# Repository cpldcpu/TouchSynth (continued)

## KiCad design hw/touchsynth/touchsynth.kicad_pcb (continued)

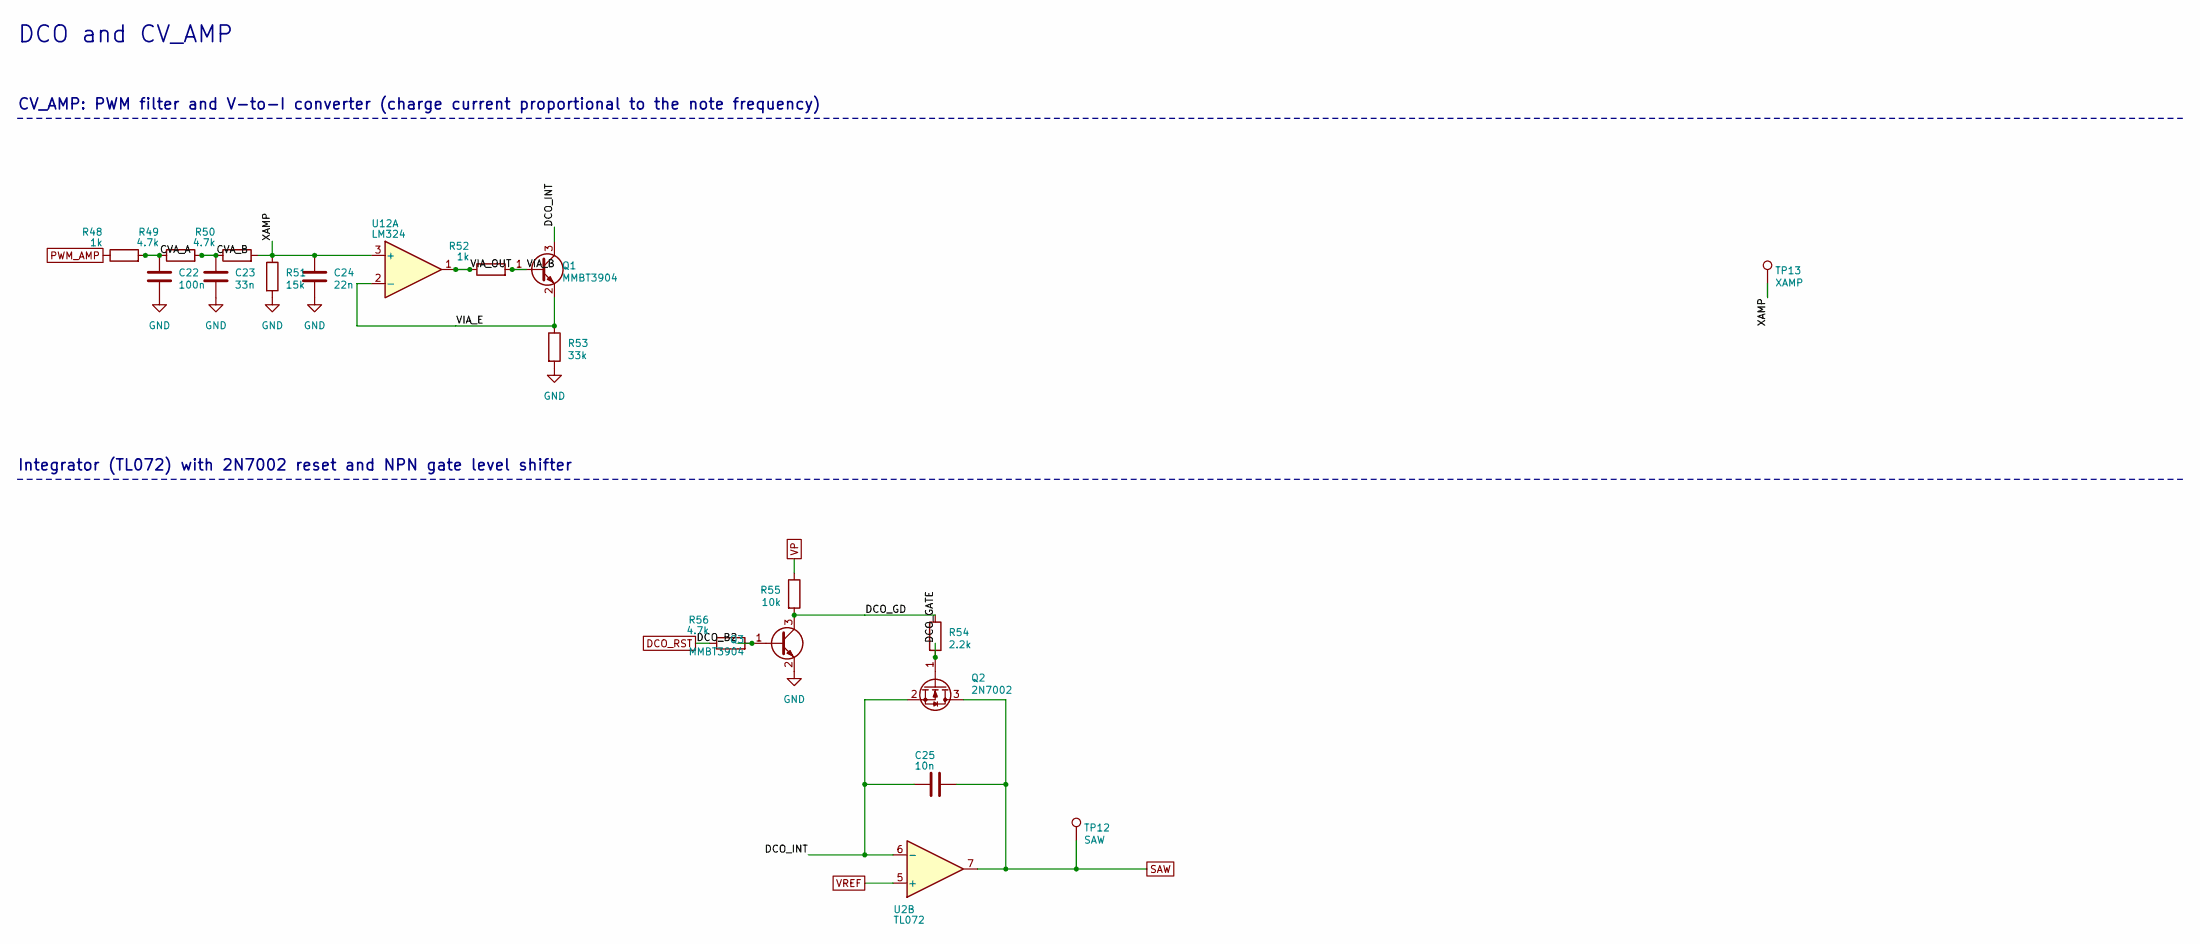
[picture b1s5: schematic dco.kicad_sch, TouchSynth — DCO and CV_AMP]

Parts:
C22: 100n; C_0603_1608Metric; LCSC C14663
C23: 33n; C_0603_1608Metric; LCSC C21117
C24: 22n; C_0603_1608Metric; LCSC C21122
C25: 10n; C_0603_1608Metric; LCSC C57112
Q1, Q3: MMBT3904; SOT-23; LCSC C20526
Q2: 2N7002; SOT-23; LCSC C8545
R48, R52: 1k; R_0603_1608Metric; LCSC C21190
R49, R50, R56: 4.7k; R_0603_1608Metric; LCSC C23162
R51: 15k; R_0603_1608Metric; LCSC C22809
R53: 33k; R_0603_1608Metric; LCSC C4216
R54: 2.2k; R_0603_1608Metric; LCSC C4190
R55: 10k; R_0603_1608Metric; LCSC C25804
TP12: SAW; TestPoint_Pad_D1.0mm
TP13: XAMP; TestPoint_Pad_D1.0mm
U2: TL072; SOIC-8_3.9x4.9mm_P1.27mm; LCSC C6961
U12: LM324; SOIC-14_3.9x8.7mm_P1.27mm; LCSC C71035

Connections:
/dco/CVA_A: C22.1, R48.2, R49.1
/dco/CVA_B: C23.1, R49.2, R50.1
/dco/DCO_B2: Q3.1 (B), R56.2
/dco/DCO_GATE: Q2.1 (G), R54.2
/dco/DCO_GD: Q3.3 (C), R54.1, R55.2
/dco/DCO_INT: C25.2, Q1.3 (C), Q2.2 (S), U2.6 (-)
/dco/VIA_B: Q1.1 (B), R52.2
/dco/VIA_E: Q1.2 (E), R53.1, U12.2 (-)
/dco/VIA_OUT: R52.1, U12.1
/dco/XAMP: C24.1, R50.2, R51.1, TP13.1, U12.3 (+)
DCO_RST: R56.1; also elsewhere on the board
GND: C22.2, C23.2, C24.2, Q3.2 (E), R51.2, R53.2; also elsewhere on the board
PWM_AMP: R48.1; also elsewhere on the board
SAW: C25.1, Q2.3 (D), TP12.1, U2.7; also elsewhere on the board
VP: R55.1; also elsewhere on the board
VREF: U2.5 (+); also elsewhere on the board

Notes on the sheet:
DCO and CV_AMP
CV_AMP: PWM filter and V-to-I converter (charge current proportional to the note frequency)
Integrator (TL072) with 2N7002 reset and NPN gate level shifter

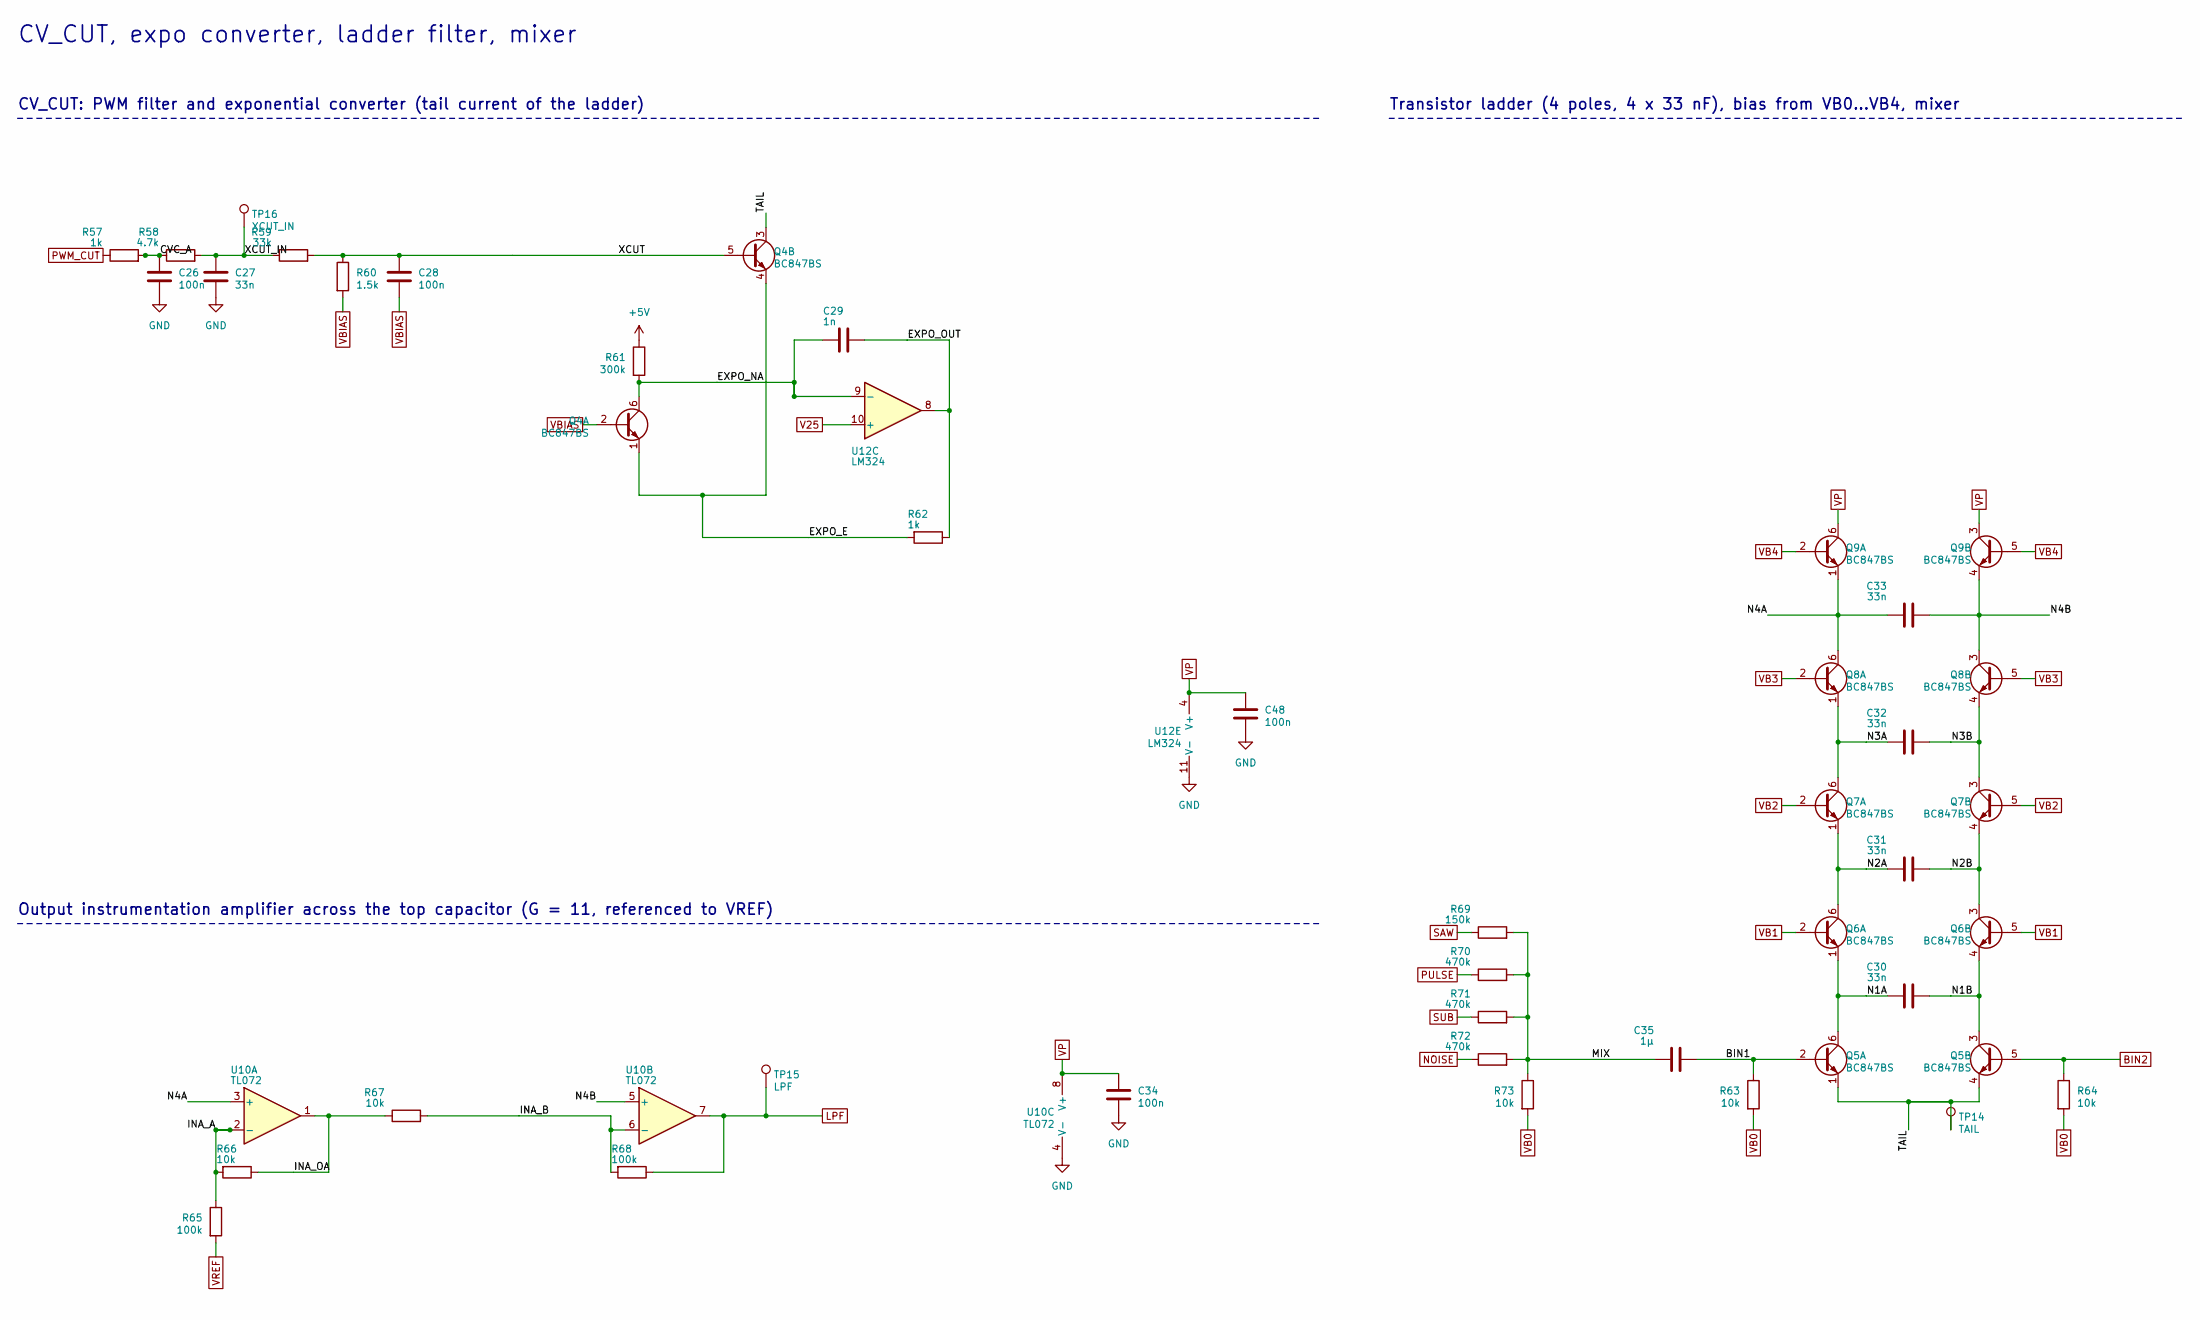
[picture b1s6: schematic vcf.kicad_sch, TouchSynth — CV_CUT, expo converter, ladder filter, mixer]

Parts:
C26, C28, C34, C48: 100n; C_0603_1608Metric; LCSC C14663
C27, C30, C31, C32, C33: 33n; C_0603_1608Metric; LCSC C21117
C29: 1n; C_0603_1608Metric; LCSC C1588
C35: 1µ; C_0603_1608Metric; LCSC C15849
Q4, Q5, Q6, Q7, Q8, Q9: BC847BS; SOT-363_SC-70-6; LCSC C41375126
R57, R62: 1k; R_0603_1608Metric; LCSC C21190
R58: 4.7k; R_0603_1608Metric; LCSC C23162
R59: 33k; R_0603_1608Metric; LCSC C4216
R60: 1.5k; R_0603_1608Metric; LCSC C22843
R61: 300k; R_0603_1608Metric; LCSC C23024
R63, R64, R66, R67, R73: 10k; R_0603_1608Metric; LCSC C25804
R65, R68: 100k; R_0603_1608Metric; LCSC C25803
R69: 150k; R_0603_1608Metric; LCSC C22807
R70, R71, R72: 470k; R_0603_1608Metric; LCSC C23178
TP14: TAIL; TestPoint_Pad_D1.0mm
TP15: LPF; TestPoint_Pad_D1.0mm
TP16: XCUT_IN; TestPoint_Pad_D1.0mm
U10: TL072; SOIC-8_3.9x4.9mm_P1.27mm; LCSC C6961
U12: LM324; SOIC-14_3.9x8.7mm_P1.27mm; LCSC C71035

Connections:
+5V: R61.1; also elsewhere on the board
/vcf/BIN1: C35.2, Q5.2 (B1), R63.1
/vcf/CVC_A: C26.1, R57.2, R58.1
/vcf/EXPO_E: Q4.1 (E1), Q4.4 (E2), R62.2
/vcf/EXPO_NA: C29.2, Q4.6 (C1), R61.2, U12.9 (-)
/vcf/EXPO_OUT: C29.1, R62.1, U12.8
/vcf/INA_A: R65.1, R66.2, U10.2 (-)
/vcf/INA_B: R67.2, R68.2, U10.6 (-)
/vcf/INA_OA: R66.1, R67.1, U10.1
/vcf/MIX: C35.1, R69.2, R70.2, R71.2, R72.2, R73.1
/vcf/N1A: C30.1, Q5.6 (C1), Q6.1 (E1)
/vcf/N1B: C30.2, Q5.3 (C2), Q6.4 (E2)
/vcf/N2A: C31.1, Q6.6 (C1), Q7.1 (E1)
/vcf/N2B: C31.2, Q6.3 (C2), Q7.4 (E2)
/vcf/N3A: C32.1, Q7.6 (C1), Q8.1 (E1)
/vcf/N3B: C32.2, Q7.3 (C2), Q8.4 (E2)
/vcf/N4A: C33.1, Q8.6 (C1), Q9.1 (E1), U10.3 (+)
/vcf/N4B: C33.2, Q8.3 (C2), Q9.4 (E2), U10.5 (+)
/vcf/TAIL: Q4.3 (C2), Q5.1 (E1), Q5.4 (E2), TP14.1
/vcf/XCUT: C28.1, Q4.5 (B2), R59.2, R60.1
/vcf/XCUT_IN: C27.1, R58.2, R59.1, TP16.1
BIN2: Q5.5 (B2), R64.1; also elsewhere on the board
GND: C26.2, C27.2, C34.2, C48.2, U10.4 (V-), U12.11 (V-); also elsewhere on the board
LPF: R68.1, TP15.1, U10.7; also elsewhere on the board
NOISE: R72.1; also elsewhere on the board
PULSE: R70.1; also elsewhere on the board
PWM_CUT: R57.1; also elsewhere on the board
SAW: R69.1; also elsewhere on the board
SUB: R71.1; also elsewhere on the board
V25: U12.10 (+); also elsewhere on the board
VB0: R63.2, R64.2, R73.2; also elsewhere on the board
VB1: Q6.2 (B1), Q6.5 (B2); also elsewhere on the board
VB2: Q7.2 (B1), Q7.5 (B2); also elsewhere on the board
VB3: Q8.2 (B1), Q8.5 (B2); also elsewhere on the board
VB4: Q9.2 (B1), Q9.5 (B2); also elsewhere on the board
VBIAS: C28.2, Q4.2 (B1), R60.2; also elsewhere on the board
VP: C34.1, C48.1, Q9.3 (C2), Q9.6 (C1), U10.8 (V+), U12.4 (V+); also elsewhere on the board
VREF: R65.2; also elsewhere on the board

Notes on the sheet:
CV_CUT, expo converter, ladder filter, mixer
CV_CUT: PWM filter and exponential converter (tail current of the ladder)
Transistor ladder (4 poles, 4 x 33 nF), bias from VB0...VB4, mixer
Output instrumentation amplifier across the top capacitor (G = 11, referenced to VREF)

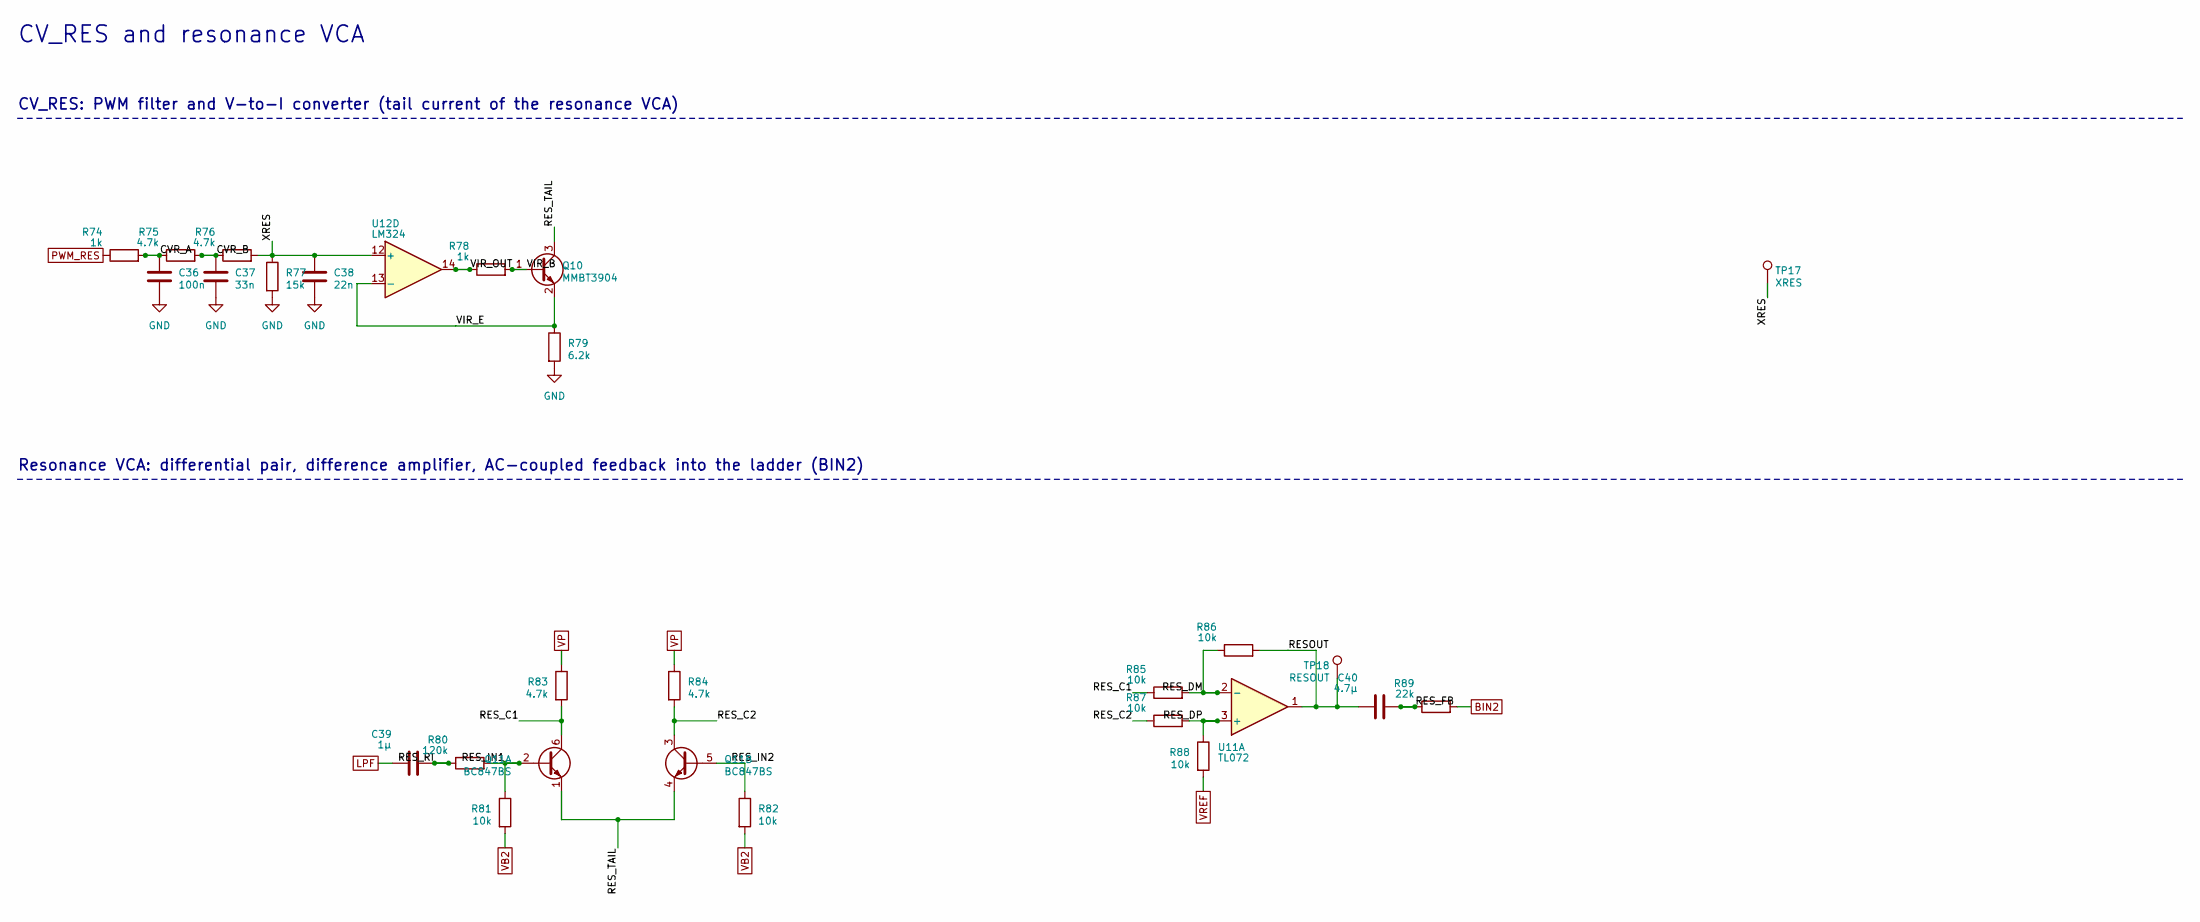
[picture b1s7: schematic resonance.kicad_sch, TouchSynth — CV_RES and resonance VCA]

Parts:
C36: 100n; C_0603_1608Metric; LCSC C14663
C37: 33n; C_0603_1608Metric; LCSC C21117
C38: 22n; C_0603_1608Metric; LCSC C21122
C39: 1µ; C_0603_1608Metric; LCSC C15849
C40: 4.7µ; C_0603_1608Metric; LCSC C19666
Q10: MMBT3904; SOT-23; LCSC C20526
Q11: BC847BS; SOT-363_SC-70-6; LCSC C41375126
R74, R78: 1k; R_0603_1608Metric; LCSC C21190
R75, R76, R83, R84: 4.7k; R_0603_1608Metric; LCSC C23162
R77: 15k; R_0603_1608Metric; LCSC C22809
R79: 6.2k; R_0603_1608Metric; LCSC C4260
R80: 120k; R_0603_1608Metric; LCSC C25808
R81, R82, R85, R86, R87, R88: 10k; R_0603_1608Metric; LCSC C25804
R89: 22k; R_0603_1608Metric; LCSC C31850
TP17: XRES; TestPoint_Pad_D1.0mm
TP18: RESOUT; TestPoint_Pad_D1.0mm
U11: TL072; SOIC-8_3.9x4.9mm_P1.27mm; LCSC C6961
U12: LM324; SOIC-14_3.9x8.7mm_P1.27mm; LCSC C71035

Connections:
/resonance/CVR_A: C36.1, R74.2, R75.1
/resonance/CVR_B: C37.1, R75.2, R76.1
/resonance/RESOUT: C40.1, R86.2, TP18.1, U11.1
/resonance/RES_C1: Q11.6 (C1), R83.2, R85.1
/resonance/RES_C2: Q11.3 (C2), R84.2, R87.1
/resonance/RES_DM: R85.2, R86.1, U11.2 (-)
/resonance/RES_DP: R87.2, R88.1, U11.3 (+)
/resonance/RES_FB: C40.2, R89.1
/resonance/RES_IN1: Q11.2 (B1), R80.2, R81.1
/resonance/RES_IN2: Q11.5 (B2), R82.1
/resonance/RES_RI: C39.2, R80.1
/resonance/RES_TAIL: Q10.3 (C), Q11.1 (E1), Q11.4 (E2)
/resonance/VIR_B: Q10.1 (B), R78.2
/resonance/VIR_E: Q10.2 (E), R79.1, U12.13 (-)
/resonance/VIR_OUT: R78.1, U12.14
/resonance/XRES: C38.1, R76.2, R77.1, TP17.1, U12.12 (+)
BIN2: R89.2; also elsewhere on the board
GND: C36.2, C37.2, C38.2, R77.2, R79.2; also elsewhere on the board
LPF: C39.1; also elsewhere on the board
PWM_RES: R74.1; also elsewhere on the board
VB2: R81.2, R82.2; also elsewhere on the board
VP: R83.1, R84.1; also elsewhere on the board
VREF: R88.2; also elsewhere on the board

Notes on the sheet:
CV_RES and resonance VCA
CV_RES: PWM filter and V-to-I converter (tail current of the resonance VCA)
Resonance VCA: differential pair, difference amplifier, AC-coupled feedback into the ladder (BIN2)

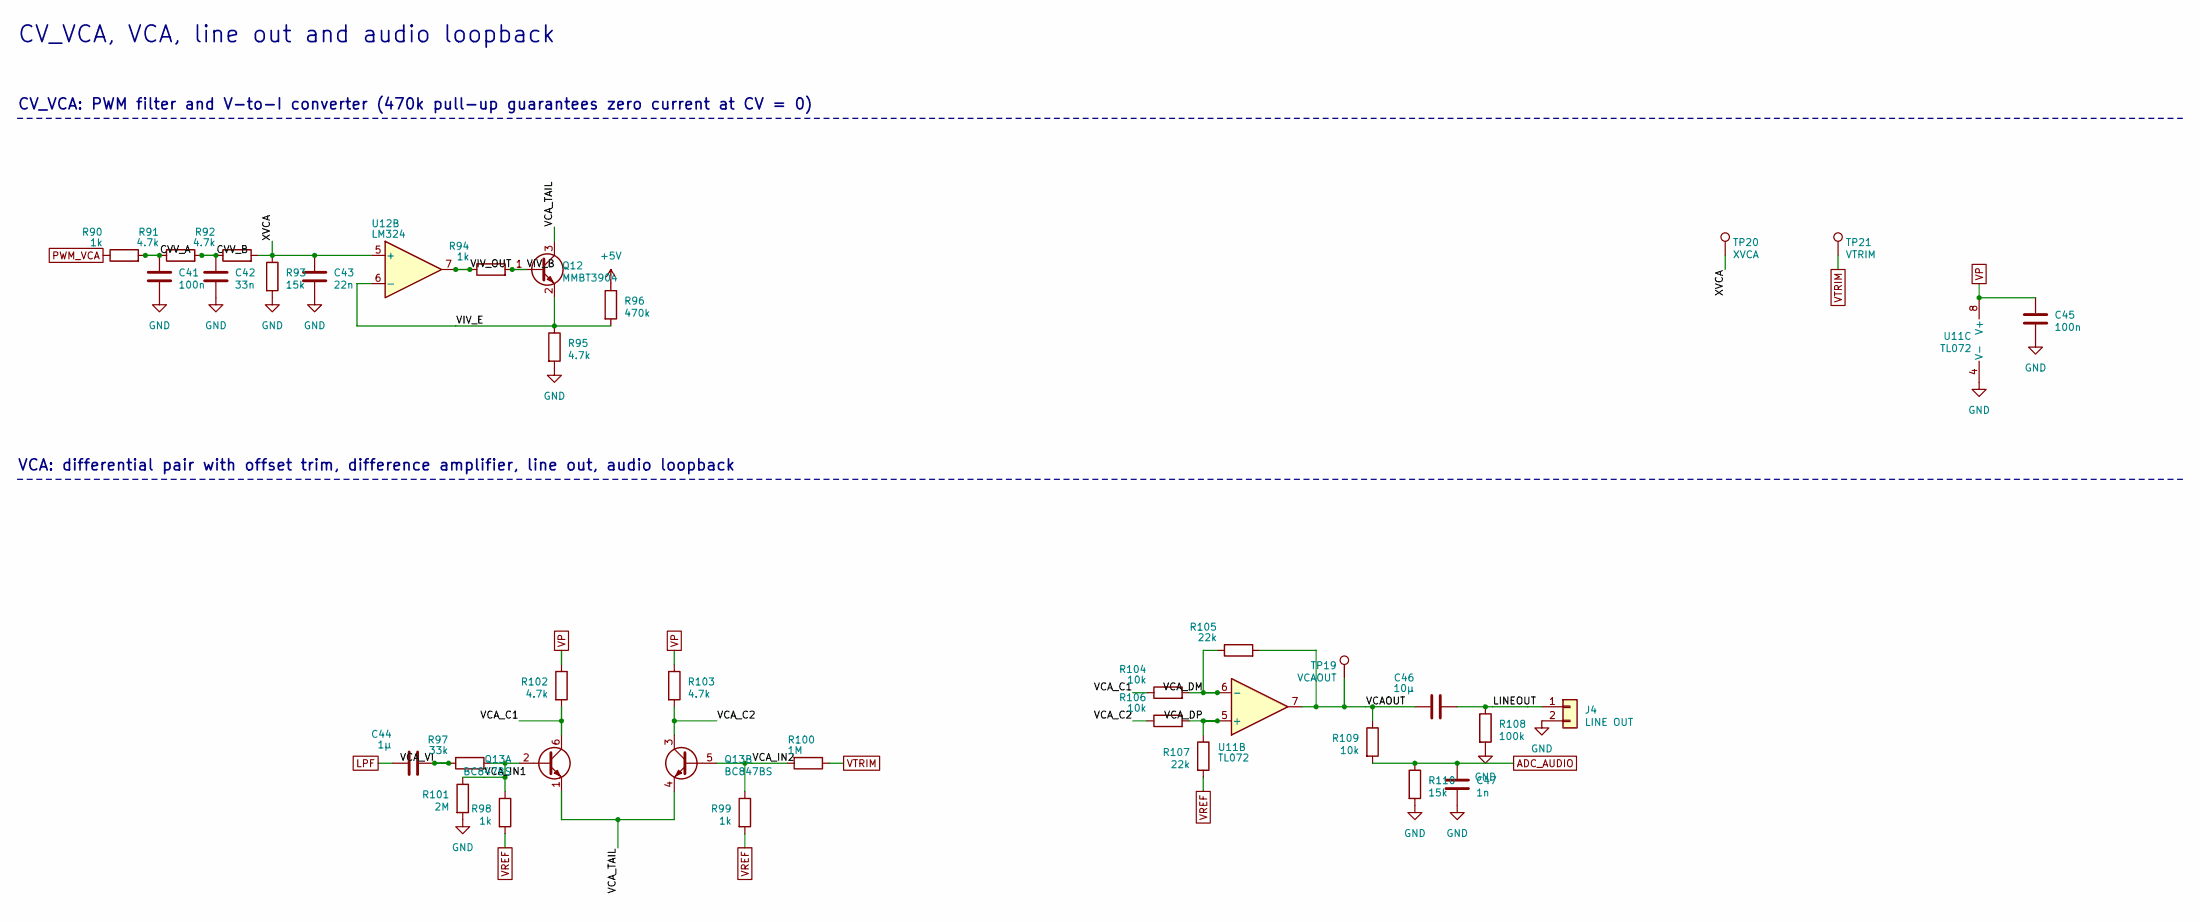
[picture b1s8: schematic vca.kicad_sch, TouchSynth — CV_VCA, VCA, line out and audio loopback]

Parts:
C41, C45: 100n; C_0603_1608Metric; LCSC C14663
C42: 33n; C_0603_1608Metric; LCSC C21117
C43: 22n; C_0603_1608Metric; LCSC C21122
C44: 1µ; C_0603_1608Metric; LCSC C15849
C46: 10µ; C_0603_1608Metric; LCSC C19702
C47: 1n; C_0603_1608Metric; LCSC C1588
J4: LINE OUT; PinHeader_1x02_P2.54mm_Vertical
Q12: MMBT3904; SOT-23; LCSC C20526
Q13: BC847BS; SOT-363_SC-70-6; LCSC C41375126
R90, R94, R98, R99: 1k; R_0603_1608Metric; LCSC C21190
R91, R92, R95, R102, R103: 4.7k; R_0603_1608Metric; LCSC C23162
R93, R110: 15k; R_0603_1608Metric; LCSC C22809
R96: 470k; R_0603_1608Metric; LCSC C23178
R97: 33k; R_0603_1608Metric; LCSC C4216
R100: 1M; R_0603_1608Metric; LCSC C22935
R101: 2M; R_0603_1608Metric; LCSC C22976
R104, R106, R109: 10k; R_0603_1608Metric; LCSC C25804
R105, R107: 22k; R_0603_1608Metric; LCSC C31850
R108: 100k; R_0603_1608Metric; LCSC C25803
TP19: VCAOUT; TestPoint_Pad_D1.0mm
TP20: XVCA; TestPoint_Pad_D1.0mm
TP21: VTRIM; TestPoint_Pad_D1.0mm
U11: TL072; SOIC-8_3.9x4.9mm_P1.27mm; LCSC C6961
U12: LM324; SOIC-14_3.9x8.7mm_P1.27mm; LCSC C71035

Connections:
+5V: R96.1; also elsewhere on the board
/vca/CVV_A: C41.1, R90.2, R91.1
/vca/CVV_B: C42.1, R91.2, R92.1
/vca/LINEOUT: C46.2, J4.1, R108.1
/vca/VCAOUT: C46.1, R105.2, R109.1, TP19.1, U11.7
/vca/VCA_C1: Q13.6 (C1), R102.2, R104.1
/vca/VCA_C2: Q13.3 (C2), R103.2, R106.1
/vca/VCA_DM: R104.2, R105.1, U11.6 (-)
/vca/VCA_DP: R106.2, R107.1, U11.5 (+)
/vca/VCA_IN1: Q13.2 (B1), R97.2, R98.1, R101.1
/vca/VCA_IN2: Q13.5 (B2), R99.1, R100.2
/vca/VCA_TAIL: Q12.3 (C), Q13.1 (E1), Q13.4 (E2)
/vca/VCA_VI: C44.2, R97.1
/vca/VIV_B: Q12.1 (B), R94.2
/vca/VIV_E: Q12.2 (E), R95.1, R96.2, U12.6 (-)
/vca/VIV_OUT: R94.1, U12.7
/vca/XVCA: C43.1, R92.2, R93.1, TP20.1, U12.5 (+)
ADC_AUDIO: C47.1, R109.2, R110.1; also elsewhere on the board
GND: C41.2, C42.2, C43.2, C45.2, C47.2, J4.2, R93.2, R95.2, R101.2, R108.2, R110.2, U11.4 (V-); also elsewhere on the board
LPF: C44.1; also elsewhere on the board
PWM_VCA: R90.1; also elsewhere on the board
VP: C45.1, R102.1, R103.1, U11.8 (V+); also elsewhere on the board
VREF: R98.2, R99.2, R107.2; also elsewhere on the board
VTRIM: R100.1, TP21.1; also elsewhere on the board

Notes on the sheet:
CV_VCA, VCA, line out and audio loopback
CV_VCA: PWM filter and V-to-I converter (470k pull-up guarantees zero current at CV = 0)
VCA: differential pair with offset trim, difference amplifier, line out, audio loopback

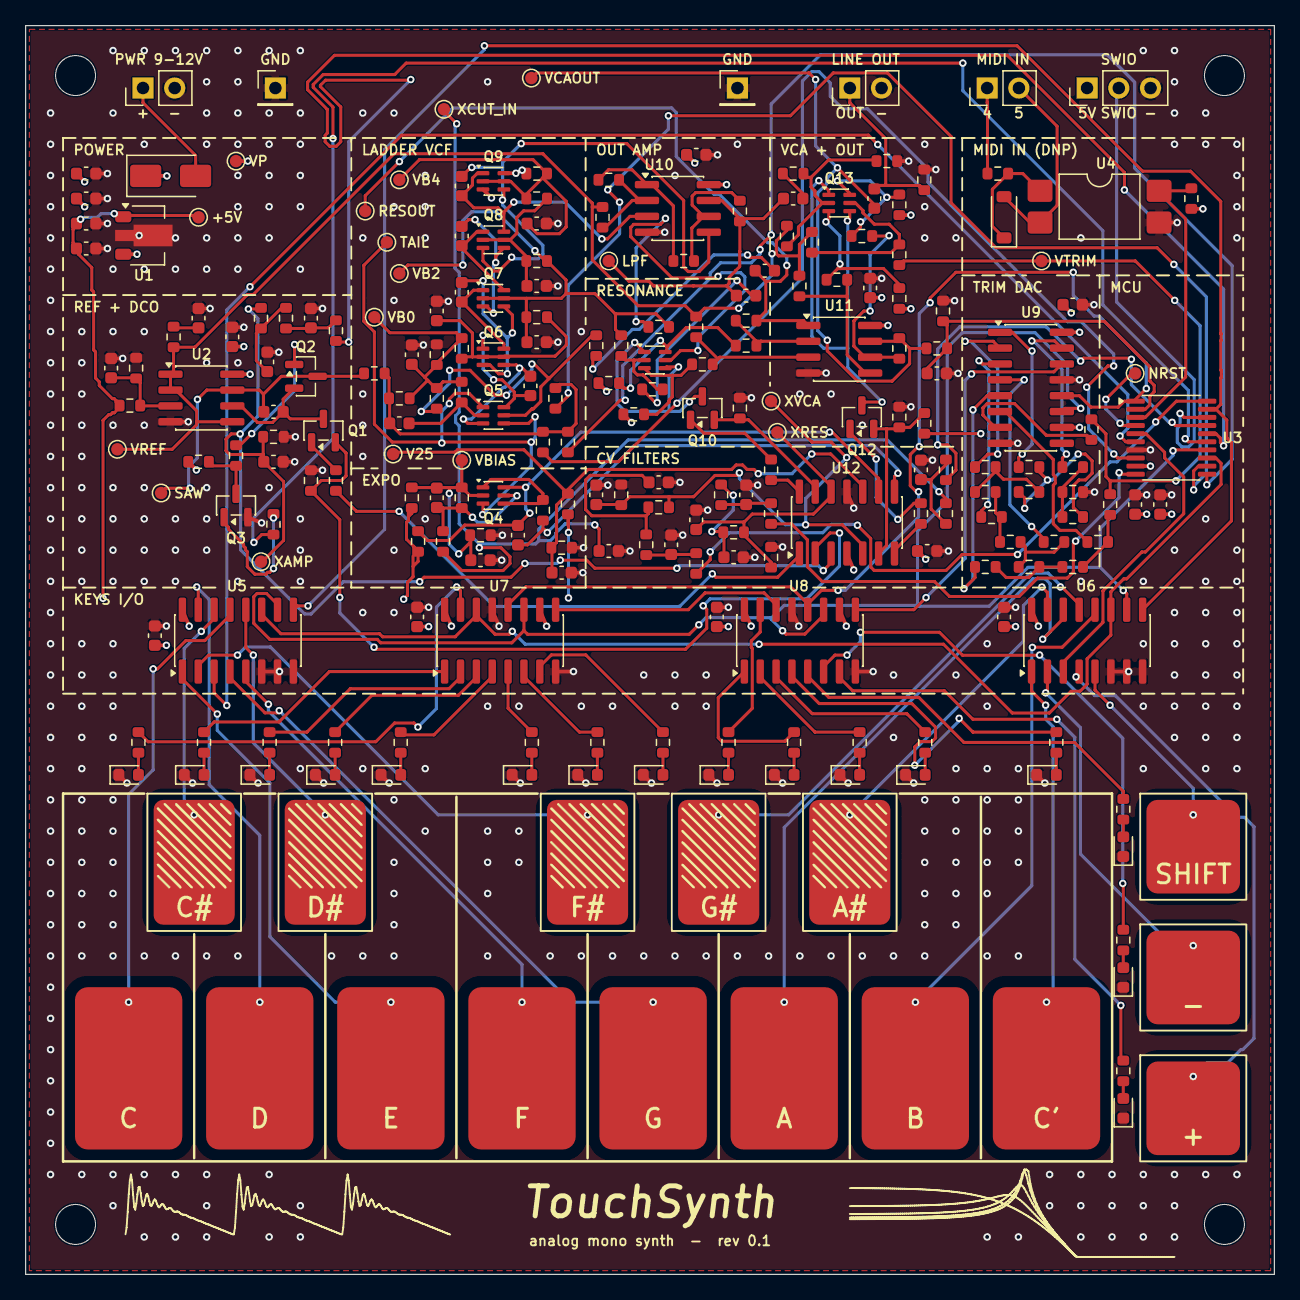
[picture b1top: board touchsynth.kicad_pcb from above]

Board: 4 copper layers, 100.0 x 100.0 mm, 246 parts (0 on the bottom side), 166 nets.

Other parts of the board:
H1, H2, H3, H4: M3; MountingHole_3.2mm_M3

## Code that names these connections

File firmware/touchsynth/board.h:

/* TouchSynth board definition: pins from hw/design.py (MCU U3, TSSOP-20), remap codes per chip family.
 *
 *  pin port  net          use                         pin port  net          use
 *   1  PD4   LATCH        74HC595 RCLK (GPIO)          11  PC1   SUB          sub-oscillator (GPIO)
 *   2  PD5   ADC_AUDIO    ADC IN5 <- audio loopback    12  PC2   PULSE        TIM2 CH2
 *   3  PD6   MIDI_RX      USART1 RX                    13  PC3   S0_DATA      mux S0 / 595 SER
 *   4  PD7   NRST                                      14  PC4   S1_CLK       mux S1 / 595 SRCLK
 *   5  PA1   TOUCH_B      mux B common, ADC IN1        15  PC5   DCO_RST      TIM2 CH1 (active low)
 *   6  PA2   TOUCH_A      mux A common, ADC IN0        16  PC6   PWM_AMP      TIM1 CH1
 *   8  PD0   NOISE        noise (GPIO)                 17  PC7   PWM_CUT      TIM1 CH2
 *  10  PC0   PWM_RES      TIM1 CH3                     18  PD1   SWIO
 *                                                       19  PD2   S2           mux S2 (GPIO)
 *                                                       20  PD3   PWM_VCA      TIM1 CH4
 *
 * Timer remaps (checked against the CH32V003 reference header and the CH32V002 datasheet pin table):
 *   CH32V003: TIM1 partial remap 1 (01b): CH1 PC6, CH2 PC7, CH3 PC0, CH4 PD3
 *             TIM2 partial remap 1 (01b): CH1 PC5, CH2 PC2
 *   CH32V00x: TIM1_RM = 0010b: TIM1_CH1_2 PC6, TIM1_CH2_2 PC7, TIM1_CH3_2 PC0, TIM1_CH4_2 PD3
 *             TIM2_RM = 010b:  TIM2_CH1_ETR_2 PC5, TIM2_CH2_2 PC2
 * The complementary / break functions these remaps also route (TIM1 CH1N PC3, CH2N PC4, CH3N PD1, BKIN PC1,
 * TIM2 CH3 PD2, CH4 PC1) are never enabled.
 */
#ifndef BOARD_H
#define BOARD_H

#include "ch32fun.h"

#define PIN_LATCH    PD4
#define PIN_AUDIO    PD5
#define PIN_MIDI_RX  PD6
#define PIN_TOUCH_B  PA1
#define PIN_TOUCH_A  PA2
#define PIN_NOISE    PD0
#define PIN_CV_RES   PC0
#define PIN_SUB      PC1
#define PIN_PULSE    PC2
#define PIN_S0_DATA  PC3
#define PIN_S1_CLK   PC4
#define PIN_DCO_RST  PC5
#define PIN_CV_AMP   PC6
#define PIN_CV_CUT   PC7
#define PIN_S2       PD2
#define PIN_CV_VCA   PD3

#define ADC_CH_TOUCH_A 0
#define ADC_CH_TOUCH_B 1
#define ADC_CH_AUDIO   5

#if defined(CH32V003)
#define CHIP_NAME "CH32V003"
#define REMAP_MASK   (AFIO_PCFR1_TIM1_REMAP | AFIO_PCFR1_TIM2_REMAP)
#define REMAP_BITS   (AFIO_PCFR1_TIM1_REMAP_PARTIALREMAP1 | AFIO_PCFR1_TIM2_REMAP_PARTIALREMAP1)
#elif defined(CH32V00x)
#if defined(CH32V002)
#define CHIP_NAME "CH32V002"
#elif defined(CH32V006)
#define CHIP_NAME "CH32V006"
#else
#define CHIP_NAME "CH32V00x"
#endif
#define REMAP_MASK   (AFIO_PCFR1_TIM1_RM | AFIO_PCFR1_TIM2_RM)
#define REMAP_BITS   (AFIO_PCFR1_TIM1_RM_1 | AFIO_PCFR1_TIM2_RM_1)       /* TIM1_RM = 0010b, TIM2_RM = 010b */
#else
#error "unsupported MCU"
#endif

/* timer register bits (identical on both families; the vendor headers name them differently) */
#define T_CEN      0x0001
#define T_UDIS     0x0002
#define T_ARPE     0x0080
#define T_CMS1     0x0020   /* centre-aligned mode 1 (counts up and down) */
#define T_UIE      0x0001
#define T_UIF      0x0001
#define T_UDE      0x0100   /* DMAINTENR: DMA request on update */
#define T_UG       0x0001
#define T_MOE      0x8000
#define T_OC_PWM1_LO  0x0068   /* OCxM = 110 (PWM1) + OCxPE, channel 1 / 3 half of CHCTLRx */
#define T_OC_PWM1_HI  0x6800   /* same for channel 2 / 4 */
#define T_CC1E     0x0001
#define T_CC1P     0x0002
#define T_CC2E     0x0010
#define T_CC3E     0x0100
#define T_CC4E     0x1000

#define F_CPU      48000000UL
#define RESET_TICKS 144        /* DCO reset pulse: 3 us at 48 MHz (same as RESET_COUNTS in tables.h) */
#define CV_PWM_TOP 1023        /* TIM1: 10 bit at 46.875 kHz, 2 more bits by dithering */

#endif

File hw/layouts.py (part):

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    xl, xr = im[0] - 5.08, o[0] + 5.08
    ci, m = ref("CI"), ref("MRST")
    yc = im[1] - 12.7
    sh.place(ci, (xl + xr) / 2, yc, 270, fields="above")          # pin 1 (SAW) right, pin 2 (INT) left
    sh.place(m, (xl + xr) / 2, yc - 17.78, 270, fields="right")    # S left, D right, G top
    sh.w(im, (xl, im[1]), (xl, sh.P(m, 2)[1]), (m, 2))
    sh.w((xl, yc), (ci, 2))
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    sh.w(b2, (b2[0] + 12.7, b2[1]))
    sh.place(rvb2, b2[0] + 5.08, b2[1] + 3.81 + 2 * U, 0, fields="left"); sh.w((b2[0] + 5.08, b2[1]), (rvb2, 1))
    sh.lbl((rvb2, 2), "VREF", (0, 1), stub=U)
    hpart(sh, rtrm, b2[0] + 12.7, b2[1], flip=True)                # pin 2 (base side) left, pin 1 (VTRIM) right
    sh.lbl(sh.P(rtrm, 1), "VTRIM", (1, 0), stub=U)
    rvc1, rvc2 = ref("RVC1"), ref("RVC2")
    for rr, c, net, fl in ((rvc1, P[6], "VCA_C1", "left"), (rvc2, P[3], "VCA_C2", "right")):
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    sh.w((p[0] + 12.7, out[1]), (jn, 1))
    sh.gnd((jn, 2))
    t = tp("VCAOUT"); sh.place(t, out[0] + 5.08, out[1] - 2 * U, fields="left"); sh.w((t, 1), (out[0] + 5.08, out[1]))
    # loopback divider to PD5
    xl = out[0] + 10.16
    rlb1, rlb2, clb = ref("RLB1"), ref("RLB2"), ref("CLB")
    sh.place(rlb1, xl, out[1] + 3.81 + U, 0, fields="left"); sh.w((xl, out[1]), (rlb1, 1))
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            sh.lbl(b1_, f"VB{k}", (-1, 0), stub=U)
            sh.lbl(b2_, f"VB{k}", (1, 0), stub=U)
            pq = ref(stages[k - 1])
            pc1, pc2 = sh.P(pq, 6), sh.P(pq, 3)
            sh.w(pc1, e1_); sh.w(pc2, e2_)
            yc = (pc1[1] + e1_[1]) / 2
            cc = ref(caps[k - 1])
            sh.place(cc, (pc1[0] + pc2[0]) / 2, yc, 90, fields="above")
            sh.w((pc1[0], yc), (cc, 1)); sh.w((cc, 2), (pc2[0], yc))
            sh.lbl((pc1[0], yc), f"N{k}A", (-1, 0), stub=0) if False else None
        if k == 4:
            sh.lbl(c1_, "VP", (0, -1), stub=U); sh.lbl(c2_, "VP", (0, -1), stub=U)
    # top nodes N4A / N4B to the instrumentation amplifier
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    sh.heading("MIDI in (not populated in rev 0.1)", 15, 190, W)
    j3 = by(lambda p: p.value == "MIDI IN")
    y = 215.9
    sh.place(j3, 35.56, y, mirror="y", fields="above")               # pin 1 (MIDI_4) at y, pin 2 below
    rin = by(lambda p: p.pins == {"1": "MIDI_4", "2": "MIDI_A"})
    dm = by(lambda p: p.lib_id == "Diode:1N4148W")
    opto = by(lambda p: p.lib_id == "Isolator:LTV-817S")
    rpu = by(lambda p: p.pins == {"1": "+5V", "2": "MIDI_RX"})
    p = hpart(sh, rin, sh.P(j3, 1)[0] + 5.08, y); sh.w((j3, 1), sh.P(rin, 1))
    sh.place(opto, p[0] + 30.48, y + U, fields="above")               # pin 1 (anode) at (p+22.86, y)
    a, k = sh.P(opto, 1), sh.P(opto, 2)
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
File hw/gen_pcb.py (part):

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    "CV_CUT filter and exponential converter", "CV_AMP filter and V-to-I converter", "Integrator and reset",
    "CV_RES filter and V-to-I converter", "Resonance VCA and difference amplifier",
    "CV_VCA filter and V-to-I converter", "VCA core and offset trim", "Difference amplifier, line out",
    "Audio loopback to PD5",
]
DIGITAL_ORDER = [
    "MCU (CH32V003 / CH32V002, hand-soldered)", "MIDI in (DNP)", "Touch multiplexers",
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]
CONNECTORS = {"PWR 9-12V": (9.4, 5.0), "LINE OUT": (66.0, 5.0), "MIDI IN": (77.0, 5.0), "SWIO": (85.0, 5.0)}
SCOPE_GND = {"left": (20.0, 5.0), "right": (57.0, 5.0)}   # well clear of the headers
PIN_NAMES = {"VIN": "+", "GND": "-", "LINEOUT": "OUT", "+5V": "5V", "MIDI_4": "4", "MIDI_5": "5"}
# In2.Cu: "NET@region" -> polygon (0.5 mm gaps between the regions): VP under the analog area, +5V under the
# right column and the keys I/O row (L shape), GND under the keyboard
PLANES_IN2 = {
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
